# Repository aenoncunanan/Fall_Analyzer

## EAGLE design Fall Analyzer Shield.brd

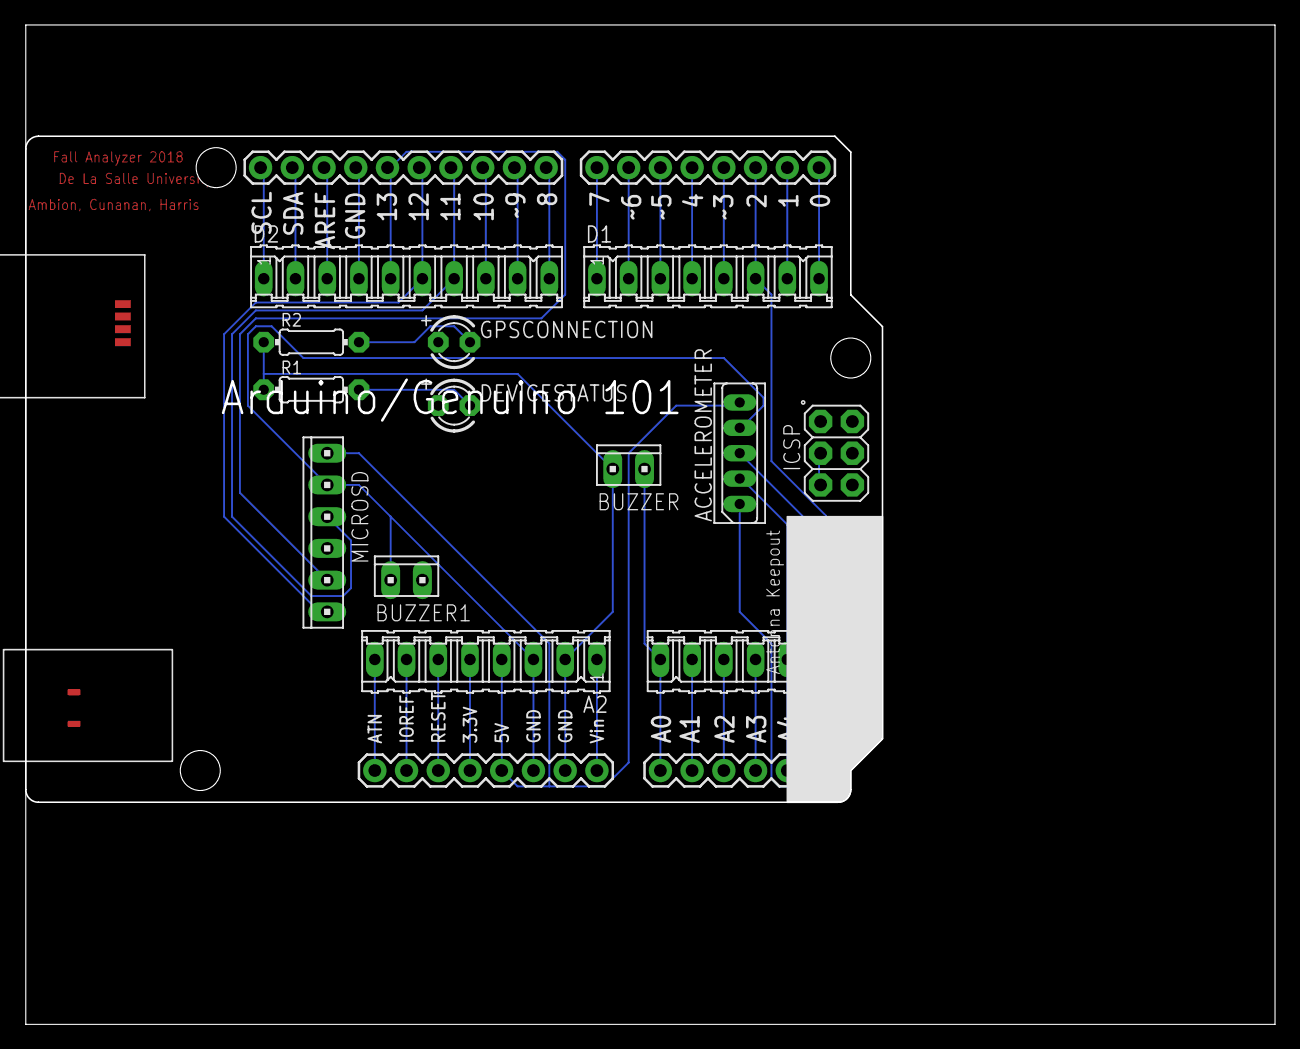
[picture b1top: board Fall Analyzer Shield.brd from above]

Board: 2 copper layers, 100.0 x 80.0 mm, 13 parts (0 on the bottom side), 35 nets.

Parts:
A1: 06P
A2: 08P
ACCELEROMETER: SPB5
BUZZER, BUZZER1: 10X02MTA
D1: 08P
D2: 10P
DEVICESTATUS: LED3MM
GPSCONNECTION: LED3MM
MICROSD: 10X06MTA
PCB1: ARDUINO_101
R1, R2: 300; 0204/7

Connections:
unnamed: A2.3, ACCELEROMETER.4, BUZZER1.2, MICROSD.2, PCB1.GND..
unnamed: DEVICESTATUS.K, R1.2
unnamed: GPSCONNECTION.K, R2.2
unnamed: A1.6, BUZZER.1, PCB1.A0
unnamed: A1.5, DEVICESTATUS.A, PCB1.A1
unnamed: A1.4, GPSCONNECTION.A, PCB1.A2
unnamed: A1.3, BUZZER1.1, PCB1.A3
unnamed: PCB1.RESET., PCB1.SCK
unnamed: A2.4, ACCELEROMETER.5, MICROSD.1, PCB1.5V
unnamed: A2.2, BUZZER.2, PCB1.GND., R1.1, R2.1
unnamed: A1.1, ACCELEROMETER.3, PCB1.A5
unnamed: A1.2, ACCELEROMETER.2, PCB1.A4
unnamed: D2.7, MICROSD.3, PCB1.11
unnamed: A2.8, PCB1.ATN
unnamed: A2.7, PCB1.I/OREF
unnamed: A2.6, PCB1.RESET
unnamed: A2.5, PCB1.3.3V
unnamed: D1.4, MICROSD.4, PCB1.4
unnamed: D2.5, MICROSD.5, PCB1.13
unnamed: D2.6, MICROSD.6, PCB1.12
unnamed: A2.1, PCB1.VIN
unnamed: D2.1, PCB1.SCL
unnamed: D2.2, PCB1.SDA
unnamed: D2.3, PCB1.AREF
unnamed: D2.4, PCB1.GND
unnamed: D2.8, PCB1.10
unnamed: D2.9, PCB1.9
unnamed: D2.10, PCB1.8
unnamed: D1.1, PCB1.7
unnamed: D1.2, PCB1.6
unnamed: D1.3, PCB1.5
unnamed: D1.5, PCB1.3
unnamed: ACCELEROMETER.1, D1.6, PCB1.2
unnamed: D1.7, PCB1.1
unnamed: D1.8, PCB1.0

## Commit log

2017-10-06 Can Detect Sit and Stand using one (1) accelerometer.
2017-10-06 Made the board to recognize wether the board is facing up, down, left, right, front, and back.
2017-10-14 Commit for push
2017-10-14 For External Accelerometer
2017-10-14 Added the external sensor to the genuino101 board
2017-10-14 Made a function for reading the built-in accelerometer and external accelerometer.
2017-10-14 Can now output: Sitting and Standing Position, using two sensors.
2017-10-23 Can now detect a fall using the on-board sensor.
2017-10-26 Started optimizing the code
2017-11-02 Started the GUI
2017-11-11 can now allow user to select storage device.
2017-11-11 user profile can now be accessed
2017-11-11 user can now set responders
2017-11-11 added the last scene for setup and deleted unnecessary lines of codes.
2017-11-12 Profile Tab in Explore Scene is now working!
2017-11-13 Working Responders Tab in Explore Window
2017-11-14 Added some security when modifying data. Moved some classes to Utils package.
2017-11-14 Started the data logger.
2017-11-15 added some fake code in Arduino_FallAnalyzer sketch
2017-11-15 Is now able to read the datalog file in sd card and store it to the tableview.
2017-11-18 updated functions in activity tab
2017-11-20 added some screenshots
2017-11-22 is now fully functioning!
2017-11-22 Updated the school logo
2017-11-22 created an executable jar file
2017-11-25 Debugged some errors. Added a checker for contact number.
2017-12-13 can now log time.
2018-01-18 Can now determine the remaining memory space. Can now output a warning if 90% of the sd card is already used.
2018-01-21 Attaching MicroSD with external Accelerometer
2018-01-22 fixed the error where activities are not being saved to the sd card
2018-01-24 Modified the GUI: edited the way of extracting the date and time, and location from datalog.
2018-02-04 for update
2018-02-13 Optimized code for the arduino. GUI initializes the filelog.txt in sd card and creates "Activities" folder
2018-02-13 modified the GUI to access multiple activity files in Activities folder
2018-02-13 Rebuilt JAR file
2018-02-17 Can now send message to multiple responders 10seconds after the fall was detected if user did not clicked the false alarm button. Can now make the speaker buzz when fall is detected.
2018-02-21 added walking and lying
2018-02-28 Paper Finalization
2018-03-06 Documents added
2018-03-06 Appendix added on paper
2018-04-24 Final Commit
